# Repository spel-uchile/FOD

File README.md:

# Femto-satellite Orbital Deployer (FOD)

This repository contains the PCB design and the source code of a femto-satellite orbital deployer or FOD. This device works by cutting a fishing line with Nichrome wire. The fishing line is normally pressing a hinge lever. When the line is cut, the hinge lever is released end the microcontroller can detect the release status.

The PCB has a transceiver (NRF24L01) to communicate with the femto-satellite once it is released. There is also a LED showing the release status, and a reset button. The energy and the comunication with the OBC is done through a molex cable with a picoblade connector.

This new version is designed for CubeSats of 2U or more. It is intended to be used as a type A interstage panel, so that it leaves more space inside the CubeSat for other payloads.

Current version: 4.0.0

### Supported software:

* KiCAD 5.99.0

### Supported hardware:

* Microcontroller: ATSAMD21G18
* Transceiver: NRF24L01
* Hinge lever: AV4524
* Mosfet: PMV16XNR

### Contact:

* Name: Matías Vidal Valladares
* e-mail: matias.vidal.v@gmail.com

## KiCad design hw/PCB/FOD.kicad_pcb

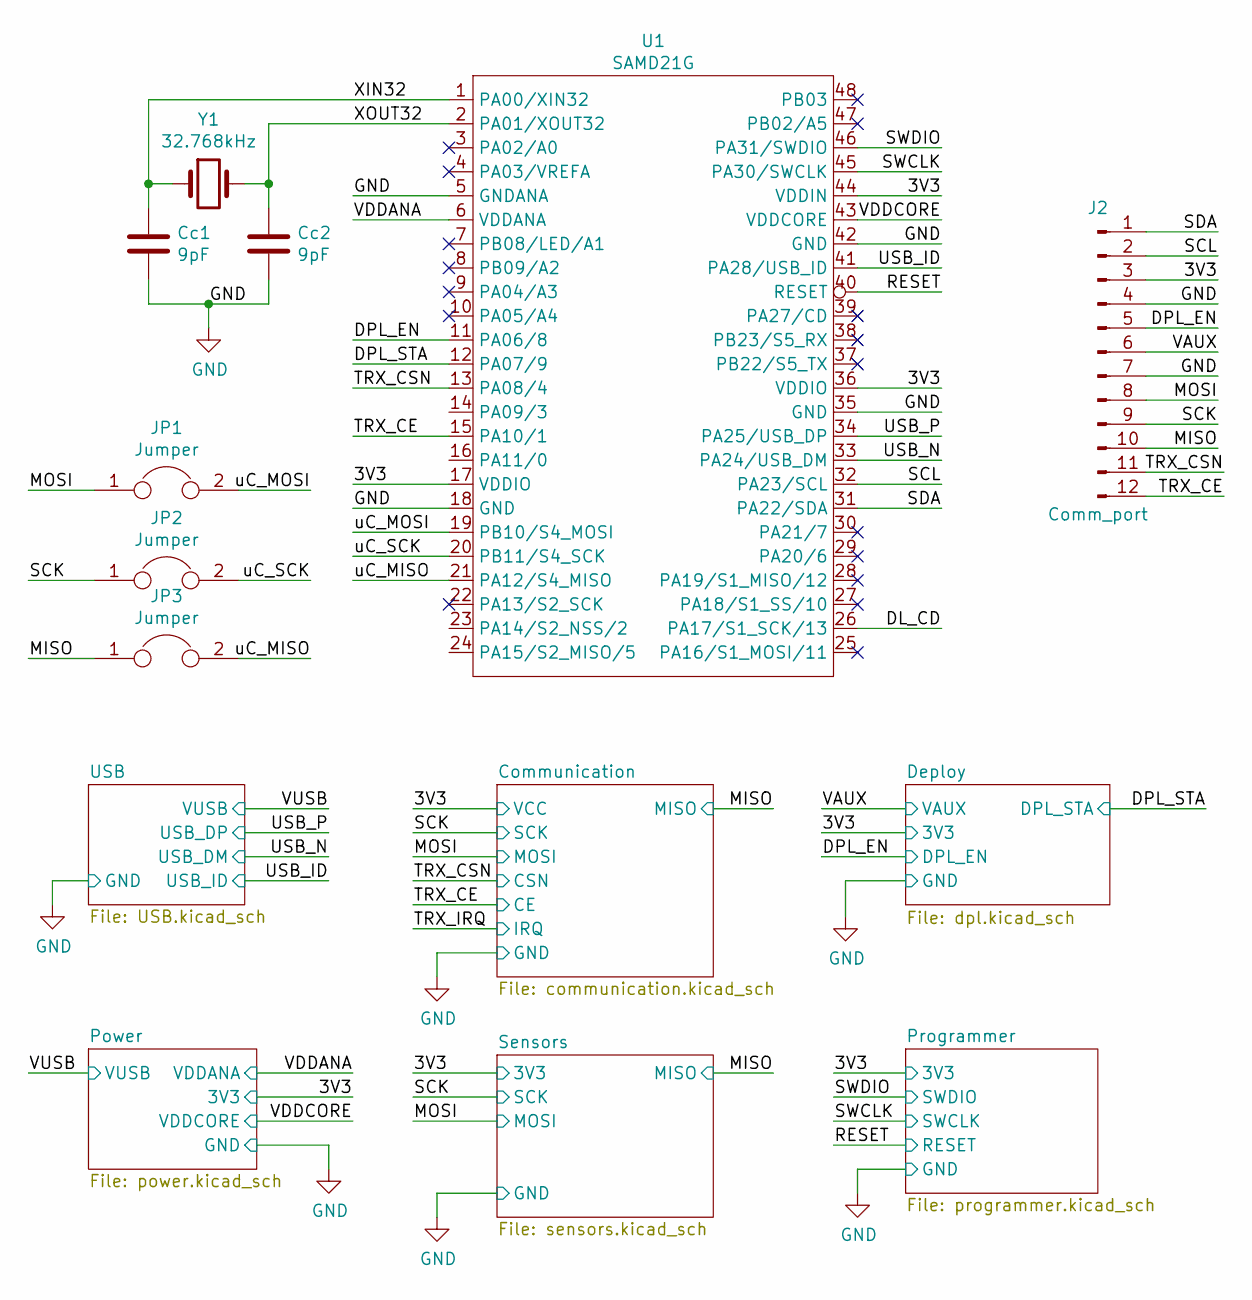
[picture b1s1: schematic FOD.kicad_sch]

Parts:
Cc1, Cc2: 9pF; C_0603_1608Metric_Pad1.05x0.95mm_HandSolder
J2: Comm_port; Molex_PicoBlade_53398-1271_1x12-1MP_P1.25mm_Vertical
JP1, JP2, JP3: Jumper; SolderJumper-2_P1.3mm_Open_RoundedPad1.0x1.5mm
U1: SAMD21G; TQFP-48_7x7mm_P0.5mm
Y1: 32.768kHz; Crystal_SMD_EuroQuartz_EQ161-2Pin_3.2x1.5mm_HandSoldering

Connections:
/3V3: J2.3, U1.17 (VDDIO), U1.36 (VDDIO), U1.44 (VDDIN); also elsewhere on the board
/DL_CD: U1.26 (PA17/S1_SCK/13)
/DPL_EN: J2.5, U1.11 (PA06/8); also elsewhere on the board
/DPL_STA: U1.12 (PA07/9); also elsewhere on the board
/MISO: J2.10, JP3.1; also elsewhere on the board
/MOSI: J2.8, JP1.1; also elsewhere on the board
/RESET: U1.40 (RESET); also elsewhere on the board
/SCK: J2.9, JP2.1; also elsewhere on the board
/SCL: J2.2, U1.32 (PA23/SCL)
/SDA: J2.1, U1.31 (PA22/SDA)
/SWCLK: U1.45 (PA30/SWCLK); also elsewhere on the board
/SWDIO: U1.46 (PA31/SWDIO); also elsewhere on the board
/TRX_CE: J2.12, U1.15 (PA10/1); also elsewhere on the board
/TRX_CSN: J2.11, U1.13 (PA08/4); also elsewhere on the board
/USB_ID: U1.41 (PA28/USB_ID); also elsewhere on the board
/USB_N: U1.33 (PA24/USB_DM); also elsewhere on the board
/USB_P: U1.34 (PA25/USB_DP); also elsewhere on the board
/VAUX: J2.6; also elsewhere on the board
/VDDANA: U1.6 (VDDANA); also elsewhere on the board
/VDDCORE: U1.43 (VDDCORE); also elsewhere on the board
/XIN32: Cc1.1, U1.1 (PA00/XIN32), Y1.1
/XOUT32: Cc2.1, U1.2 (PA01/XOUT32), Y1.2
/uC_MISO: JP3.2, U1.21 (PA12/S4_MISO)
/uC_MOSI: JP1.2, U1.19 (PB10/S4_MOSI)
/uC_SCK: JP2.2, U1.20 (PB11/S4_SCK)
GND: Cc1.2, Cc2.2, J2.4, J2.7, J2.MP, U1.5 (GNDANA), U1.18 (GND), U1.35 (GND), U1.42 (GND); also elsewhere on the board

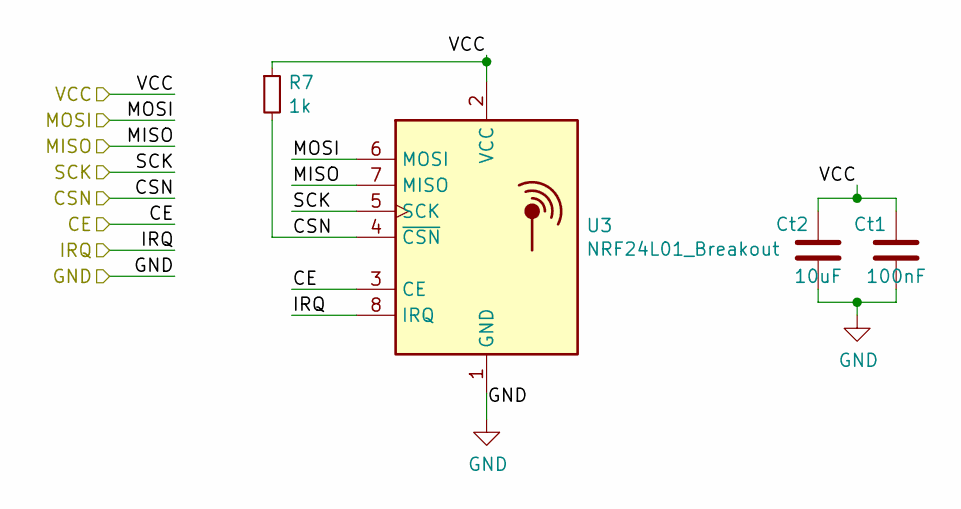
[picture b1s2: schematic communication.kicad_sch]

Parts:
Ct1: 100nF; C_0603_1608Metric_Pad1.05x0.95mm_HandSolder
Ct2: 10uF; C_0603_1608Metric_Pad1.05x0.95mm_HandSolder
R7: 1k; R_0603_1608Metric_Pad1.05x0.95mm_HandSolder
U3: NRF24L01_Breakout; nRF24L01_Breakout

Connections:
/3V3: Ct1.2, Ct2.2, R7.1, U3.2 (VCC); also elsewhere on the board
/MISO: U3.7 (MISO); also elsewhere on the board
/MOSI: U3.6 (MOSI); also elsewhere on the board
/SCK: U3.5 (SCK); also elsewhere on the board
/TRX_CE: U3.3 (CE); also elsewhere on the board
/TRX_CSN: R7.2, U3.4 (~CSN); also elsewhere on the board
/TRX_IRQ: U3.8 (IRQ)
GND: Ct1.1, Ct2.1, U3.1 (GND); also elsewhere on the board

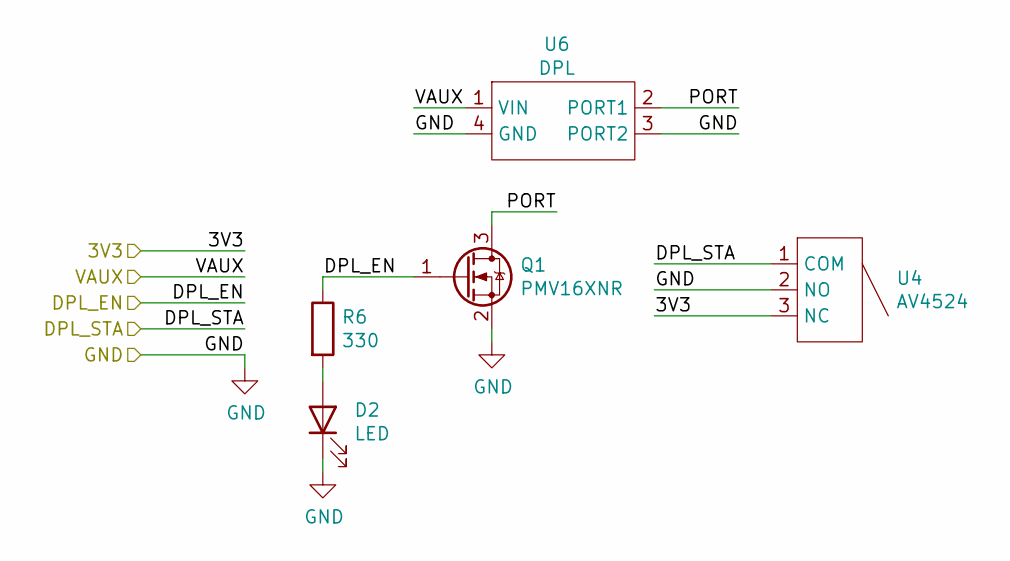
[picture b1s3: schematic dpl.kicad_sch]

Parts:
D2: LED; D_0805_2012Metric_Pad1.15x1.40mm_HandSolder
Q1: PMV16XNR; SOT-23
R6: 330; R_0603_1608Metric_Pad1.05x0.95mm_HandSolder
U4: AV4524
U6: DPL; Type-A_middle_port

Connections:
/3V3: U4.3 (NC); also elsewhere on the board
/DPL_EN: Q1.1 (G), R6.1; also elsewhere on the board
/DPL_STA: U4.1 (COM); also elsewhere on the board
/Deploy/PORT: Q1.3 (D), U6.2 (PORT1)
/VAUX: U6.1 (VIN); also elsewhere on the board
GND: D2.1 (K), Q1.2 (S), U4.2 (NO), U6.3 (PORT2), U6.4 (GND); also elsewhere on the board
unnamed: D2.2 (A), R6.2

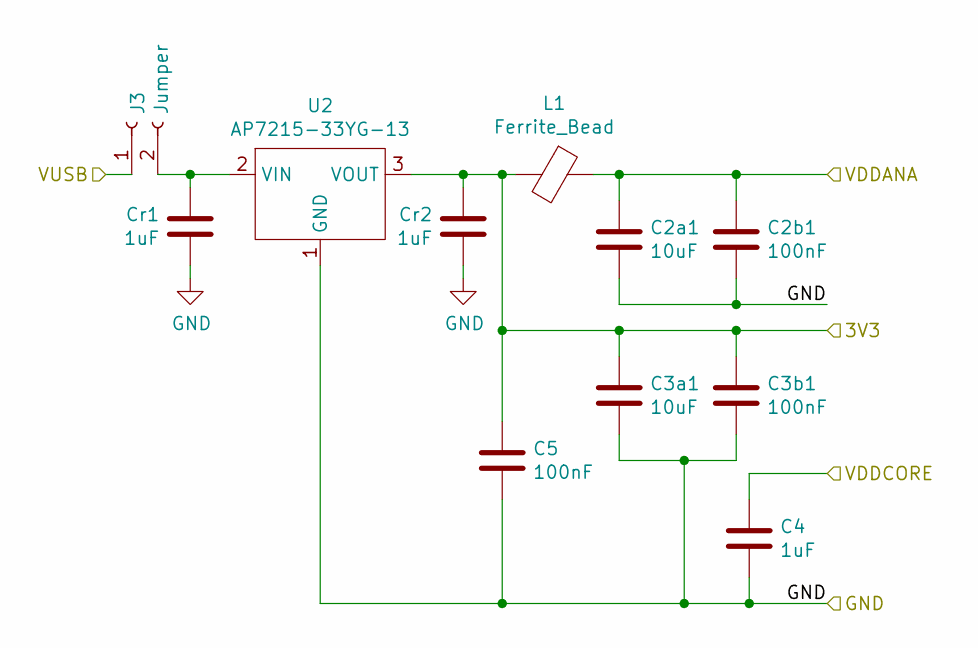
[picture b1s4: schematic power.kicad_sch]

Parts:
C2a1, C3a1: 10uF; C_0603_1608Metric_Pad1.05x0.95mm_HandSolder
C2b1, C3b1, C5: 100nF; C_0603_1608Metric_Pad1.05x0.95mm_HandSolder
C4: 1uF; C_0603_1608Metric_Pad1.05x0.95mm_HandSolder
Cr1, Cr2: 1uF; C_0603_1608Metric_Pad1.05x0.95mm_HandSolder
J3: Jumper; PinHeader_1x02_P2.54mm_Vertical
L1: Ferrite_Bead; L_0805_2012Metric_Pad1.15x1.40mm_HandSolder
U2: AP7215-33YG-13; SOT-89-3

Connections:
/3V3: C3a1.1, C3b1.1, C5.1, Cr2.1, L1.2, U2.3 (VOUT); also elsewhere on the board
/VDDANA: C2a1.1, C2b1.1, L1.1; also elsewhere on the board
/VDDCORE: C4.1; also elsewhere on the board
/VUSB: J3.1; also elsewhere on the board
GND: C2a1.2, C2b1.2, C3a1.2, C3b1.2, C4.2, C5.2, Cr1.2, Cr2.2, U2.1 (GND); also elsewhere on the board
unnamed: Cr1.1, J3.2, U2.2 (VIN)

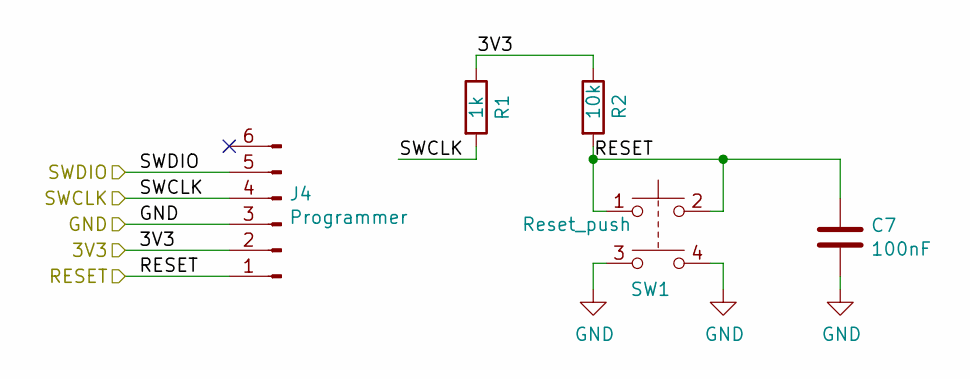
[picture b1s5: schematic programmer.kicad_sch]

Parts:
C7: 100nF; C_0603_1608Metric_Pad1.05x0.95mm_HandSolder
J4: Programmer; Molex_PicoBlade_53398-0671_1x06-1MP_P1.25mm_Vertical
R1: 1k; R_0603_1608Metric_Pad1.05x0.95mm_HandSolder
R2: 10k; R_0603_1608Metric_Pad1.05x0.95mm_HandSolder
SW1: Reset_push; SW_TH_Tactile_Omron_B3F-10xx

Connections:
/3V3: J4.2, R1.1, R2.1; also elsewhere on the board
/RESET: C7.1, J4.1, R2.2, SW1.1, SW1.2; also elsewhere on the board
/SWCLK: J4.4, R1.2; also elsewhere on the board
/SWDIO: J4.5; also elsewhere on the board
GND: C7.2, J4.3, J4.MP, SW1.3, SW1.4; also elsewhere on the board

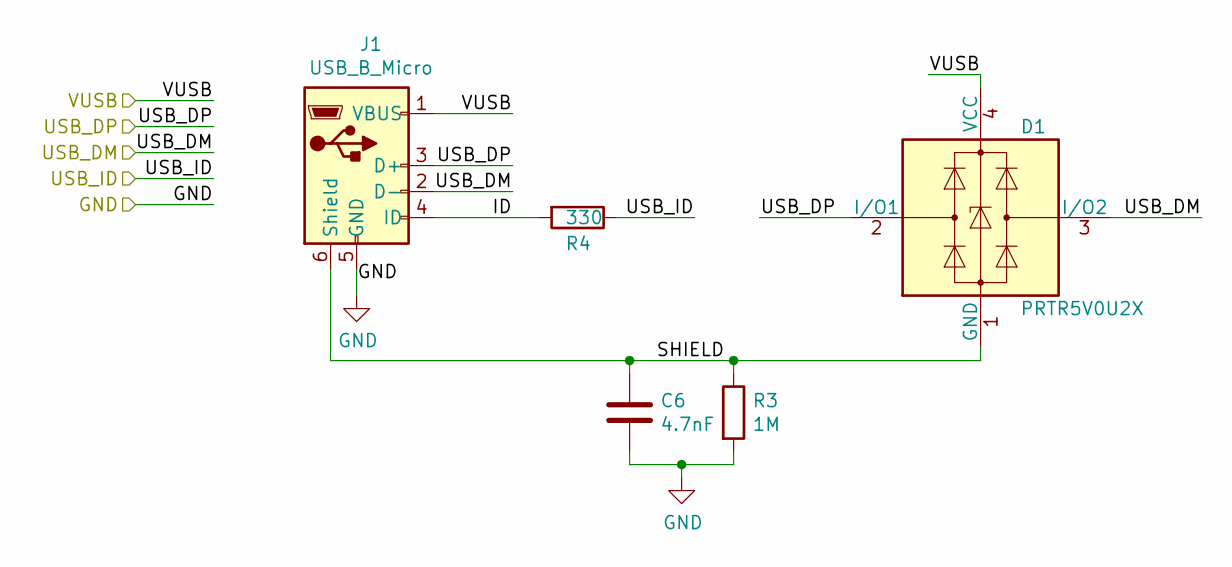
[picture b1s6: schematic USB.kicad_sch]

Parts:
C6: 4.7nF; C_0603_1608Metric_Pad1.05x0.95mm_HandSolder
D1: PRTR5V0U2X; SOT-143
J1: USB_B_Micro; USB_Micro-B_Molex_47346-0001
R3: 1M; R_0603_1608Metric_Pad1.05x0.95mm_HandSolder
R4: 330; R_0603_1608Metric_Pad1.05x0.95mm_HandSolder

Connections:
/USB/ID: J1.4 (ID), R4.2
/USB/SHIELD: C6.1, D1.1 (GND), J1.6 (Shield), R3.1
/USB_ID: R4.1; also elsewhere on the board
/USB_N: D1.3 (I/O2), J1.2 (D-); also elsewhere on the board
/USB_P: D1.2 (I/O1), J1.3 (D+); also elsewhere on the board
/VUSB: D1.4 (VCC), J1.1 (VBUS); also elsewhere on the board
GND: C6.2, J1.5 (GND), R3.2; also elsewhere on the board

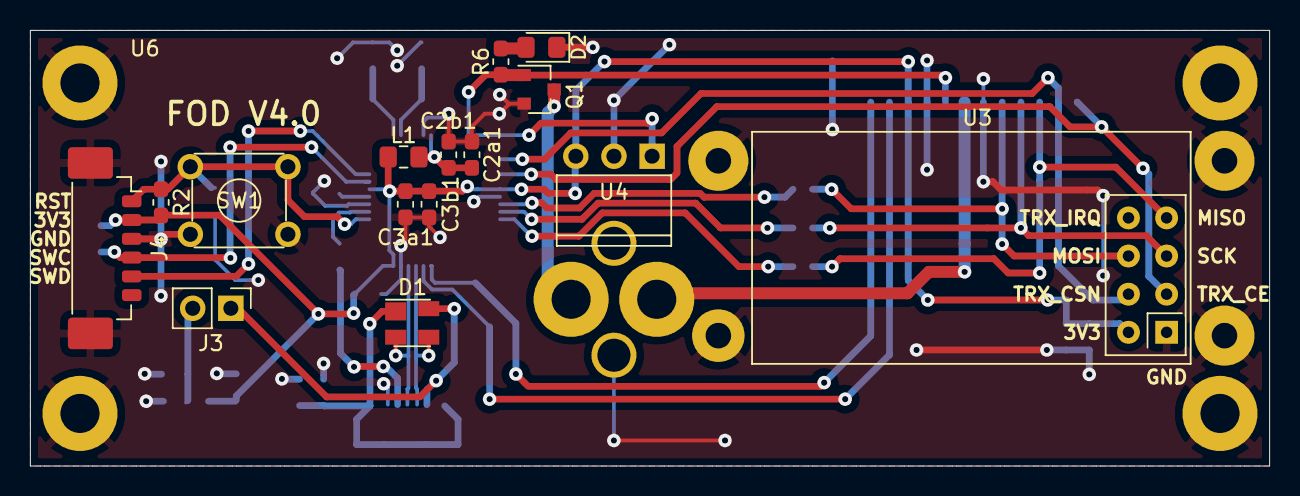
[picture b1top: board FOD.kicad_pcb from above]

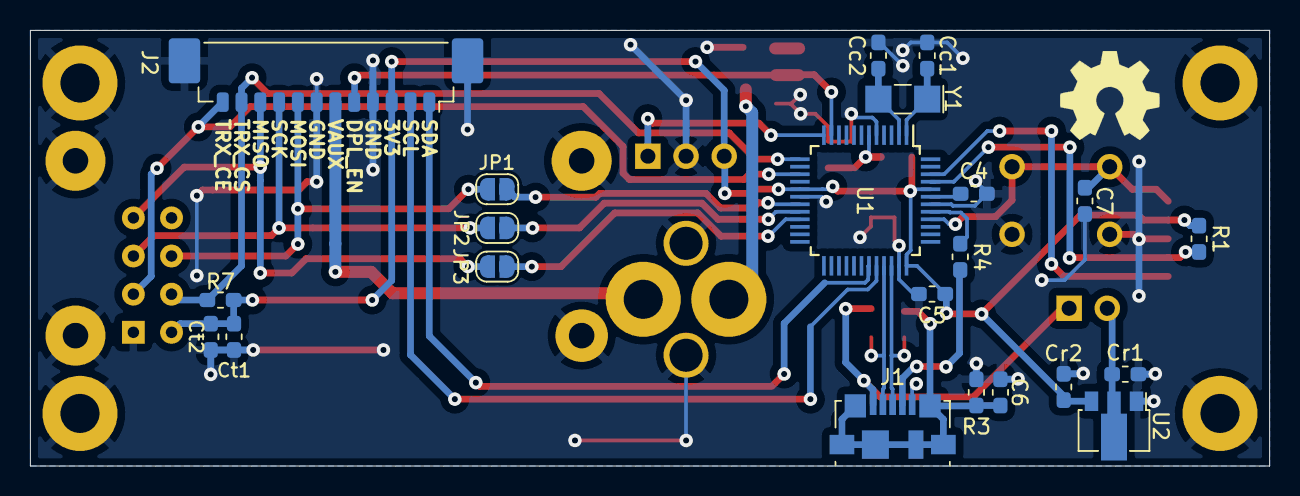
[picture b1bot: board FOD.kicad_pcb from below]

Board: 2 copper layers, 82.5 x 29.0 mm, 38 parts (22 on the bottom side), 31 nets.

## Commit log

2018-10-25 Added some basic software files.
2018-10-25 Added a basic PCB schematic.
2018-10-25 CAD files
    CAD files
2018-10-26 Added preliminary design of the PC104 board connections.
2018-11-09 Updated the FOD's PCB.
2018-11-12 Moved the payload library to its own folder.
2018-11-12 Added deploy system to schematic.
2018-11-12 Added Payload library symbol for the PC104 stack standard.
2018-11-12 Updated PCB's schematic.
2018-11-12 Added pin labels for the femto-satellite deploy system.
2018-11-14 Improved the FOD's PCB boundaries based on the new payload standard for the SUCHAI 2 and 3. Added silk mask for the stack and the holes. Added space for better cable management.
2018-11-14 Updated the connections and the footprints asignation.
2018-11-15 Created library for the high power resistor used in the deploy system.
2018-11-15 Added the deployment system to the board's footprint.
2018-11-15 Added a library for the SAMD21 microcontroller and for a power regulator.
2018-11-16 Changed outer line from the libraries to Edge.Cuts. Increased the drill size of the mechanical holes.
2018-11-19 Added new connections and 3D models. Most components are now placed in the PCB.
2018-11-20 Fixed error in edge cuts, and updated the pads' size of the mechanical holes.
2018-11-20 Added preliminary CAD design of the FOD's PCB.
2018-11-20 Fixed error in pin spacing (changed from 2.56 mm to 2.54 mm).
2018-11-20 Fixed some dimensions of the FOD's PCB.
2018-11-20 Updated the preliminary FOD's PCB CAD.
2018-11-21 Added switch to detect the deplyment status. Routed all connections.
2018-11-22 Made space for the interrupter.
2018-11-22 Fixed space conflict between the interrupter and the voltage regulator.
2018-11-28 Changed the NPTH holes to Through-holes to connect them to ground.
2018-11-28 Updated the PCB with the thorugh-holes connected to ground.
2018-11-28 Exported PCB's CAD model.
2018-11-28 Added silk layer with pin labels.
2018-11-28 Ploted new gerber files.
2018-11-28 Reduced the size of some drill holes.
2018-11-28 Exported the corrected version of the PCB in Step file format.
2018-12-14 Fixed error in library import. Updated FOD pins and changed Serial statements to SerialUSB.
2018-12-14 Added deployment pins.
2019-06-05 Updated the RFM69HCW symbol and created a new SAMD21E symbol.
2019-06-14 Increased drill and pad size for the PC104 stack.
2019-06-14 Increased PC104 pad's and drill's size.
2019-07-05 Updated the symbol and footprint of the PC104 standard.
2019-07-08 Finished preliminary design phase for the version 2.0.
2019-07-09 Replaced the SMA connector with an U.FL connector. Added some layout improvements.
2019-07-09 Moved the drill holes for the nylon wire. Generated the Gerber files.
2019-07-09 Generated a new CAD file for the 2.0 version of the PCB.
2019-07-11 Added a label for the deployment status LED.
2019-07-12 Reploted the gerber files to add a silk label.
2019-07-12 Added a new CAD file for the femto-satellite orbital deployer v2.0.
2019-07-12 Ordered the folder. Separated the libraries from the main file. Created a new library for the deployment system.
2019-07-18 Moved some missplaced silk labels.
2019-07-18 New CAD for the FOD.
2019-07-18 Fixed a small issue about the pin assignation of the deployment sensor. Change the position of some vias so that they are not too close to some tracks.
2019-07-19 Fixed multiple errors in the FOD class and in the arduino file.
2019-07-19 Enlarged the drill hole and the pad's size of the interrupter.
2019-07-19 Exported new CAD file.
2019-08-02 Fixed and added functions to change the mode of operation of the FOD. For now it only affects the transceiver.
2019-08-05 Added more modes of operation. Fixed some minor errors.
2019-08-28 Fixed some errors and added serial commands.
2019-09-03 Removed gps library. Decreased timeout for the serial communication.
2019-09-03 Added more commands to adjust the on time and to receive gps data from I2C or Serial communication.
2019-09-18 Implemented a function that handles the received commands, Serial and I2C. Changed the way the method setOnTime works.
2019-09-23 Solved some compilation errors due to old struct parameters that were deprecated.
2019-09-24 Fixed errors in the I2C communication. Added more parameters to send to the OBC such as the current on-time and the number of attempts
2019-09-24 Reorder the commands considering the priority in execution time. Added the GET_CONFIG command.
2019-09-25 Added a delay at the start of the program for stability.
2020-03-22 Created a new PCB for the Femto-satellite Orbital Deployer (FOD). Instead of using the PC104 standard, it now has the shape of a type A interstage panel. Added a data logger. Deleted old files from t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
2020-03-22 Created a new CAD for the 3.0 version. Deleted old CAD.
2020-03-26 Improved the trace routing to increase the ground plane. Added text labels for some connectors.
2020-03-26 Generated new gerber files. Updated the step file.
2020-03-27 Separated the VIN power line into two independent power lines (VAUX and VAUX2). This is done to add compatibility with other CubeSats standards. Added the option to bridge those lines with a zero Ohm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
2020-03-27 Generated new gerber and CAD files.
2020-04-25 Removed backup files.
2020-04-25 Added a picture for the README file.
2020-04-25 Added a picture of the new FOD system. Added a more detailed description.
2020-04-25 Added a description about the shape of the new FOD.
2021-10-07 Added an image for the new PCB version and updated the README file.
2021-10-07 Updated the gerber files.
2021-10-07 FOD's new PCB version.
2021-10-07 New files for the new FOD PCB.
2021-10-07 Removed the data logger and updated the libraries.
2021-10-07 Deleted old files and added a BOM.
2021-10-07 Updated the CAD file.
